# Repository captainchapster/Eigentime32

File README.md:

# Eigentime32

A self-contained digital pocket watch that keeps its own time for a decade. No GPS, one CR2032, one PCB.

*Eigentime* (proper time) is the time a clock measures along its own path, with no outside reference. That is the whole idea here.

## At a glance
| | |
|---|---|
| Timekeeping | Micro Crystal RV-3032-C7 TCXO RTC, ±1.5 ppm (0–50 °C), ~160 nA |
| Display | Sharp LS013B7DH03 1.28" 128×128 memory LCD, powered only while the lid is open |
| MCU | STM32L031G6 (proposed) |
| Wake | Normally-closed reed switch + magnet in the lid |
| Power | CR2032, ~1 µA average, ~10-year target |
| Recalibration | ST25DV04K NFC tag: set time and trim drift from a phone, about once a year |
| Size | 43.9 mm round × 10.8 mm thick with the lid shut (3D-printed hunter case, see `case/`) |

## Accuracy
Aging of the crystal, not temperature, dominates over ten years. With one calibration at build time and a yearly NFC recalibration the target is roughly ±30 s/yr. See [docs/power-pins-accuracy.md](docs/power-pins-accuracy.md).

## Repository layout
- `docs/` design notes and decisions
- `hardware/` KiCad project, BOM
- `firmware/` MCU firmware
- `case/` 3D-printed case: parametric CadQuery model, fit check, printable STL/STEP

## Status
Architecture defined, schematic not started. See [docs/decisions.md](docs/decisions.md).

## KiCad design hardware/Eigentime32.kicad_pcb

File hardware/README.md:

# Hardware

KiCad project goes here (`Eigentime32.kicad_pro`). Schematic order: power → RTC → MCU → LCD → lid/buttons → NFC.

Board: ~40 mm round, 0.8 mm, 2 layers. Front side bare under the LCD; all parts on the back around the CR2032 holder.

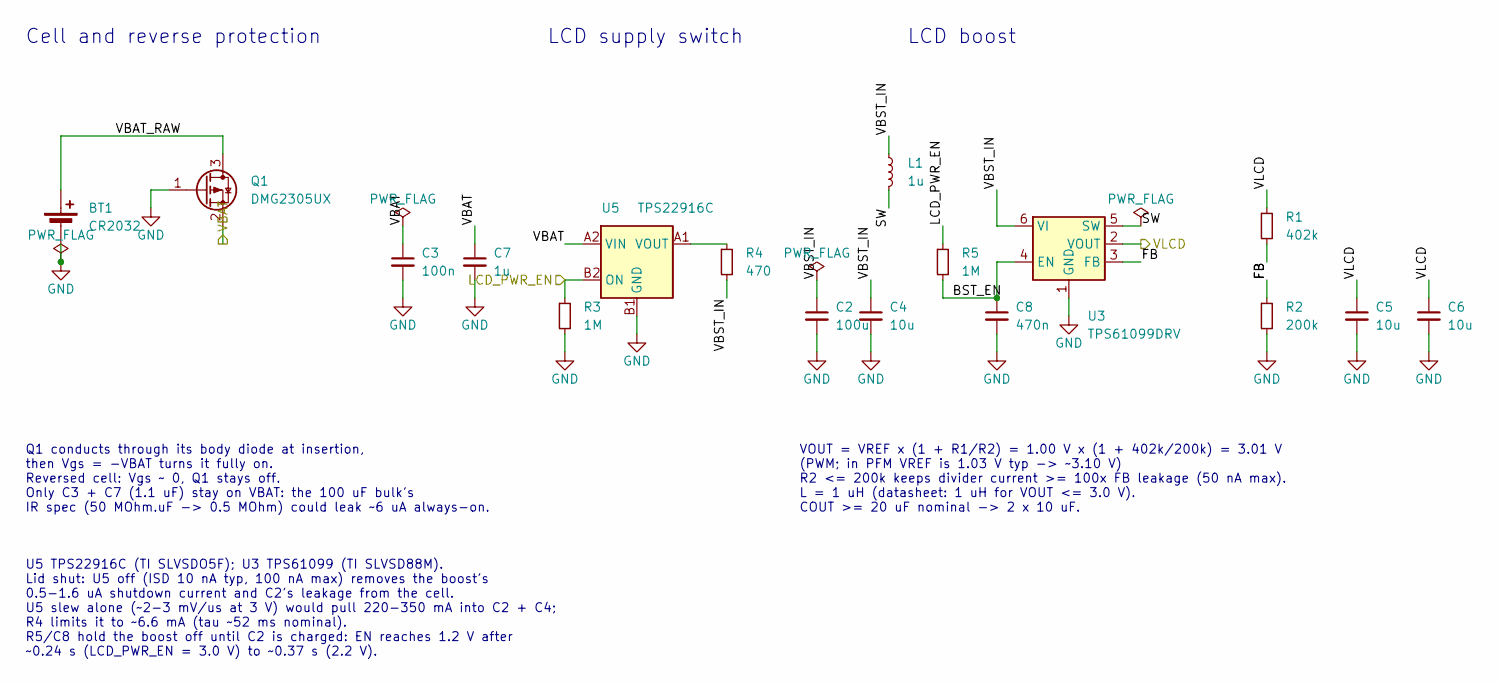
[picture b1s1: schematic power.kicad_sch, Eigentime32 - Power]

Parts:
BT1: CR2032; BatteryHolder_Keystone_3034_1x20mm_SmallNegPad; MPN 3034
C2: 100u; C_1206_3216Metric; MPN CL31A107MQHNNNE
C3: 100n; C_0402_1005Metric; MPN GRM155R71C104KA88D
C4, C5, C6: 10u; C_0603_1608Metric; MPN GRM188R60J106ME84D
C7: 1u; C_0402_1005Metric; MPN GRM155R61A105KE15D
C8: 470n; C_0402_1005Metric; MPN GRM155R61A474KE15D
L1: 1u; L_Wuerth_MAPI-2512; MPN 74404024010
Q1: DMG2305UX; SOT-23; MPN DMG2305UX-7
R1: 402k; R_0402_1005Metric; MPN RC0402FR-07402KL
R2: 200k; R_0402_1005Metric; MPN RC0402FR-07200KL
R3, R5: 1M; R_0402_1005Metric; MPN RC0402FR-071ML
R4: 470; R_0402_1005Metric; MPN RC0402FR-07470RL
U3: TPS61099DRV; WSON-6-1EP_2x2mm_P0.65mm_EP1x1.6mm; MPN TPS61099DRVR
U5: TPS22916C; Texas_PicoStar_BGA-4_0.758x0.758mm_Layout2x2_P0.4mm; MPN TPS22916CYFPR

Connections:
/LCD_PWR_EN: R3.1, R5.1, U5.B2 (ON); also elsewhere on the board
/Power/BST_EN: C8.1, R5.2, U3.4 (EN)
/Power/FB: R1.2, R2.1, U3.3 (FB)
/Power/SW: L1.2, U3.5 (SW)
/Power/VBAT_RAW: BT1.1 (+), Q1.3 (D)
/Power/VBST_IN: C2.1, C4.1, L1.1, R4.2, U3.6 (VI)
/VBAT: C3.1, C7.1, Q1.2 (S), U5.A2 (VIN); also elsewhere on the board
/VLCD: C5.1, C6.1, R1.1, U3.2 (VOUT); also elsewhere on the board
GND: BT1.2 (-), C2.2, C3.2, C4.2, C5.2, C6.2, C7.2, C8.2, Q1.1 (G), R2.2, R3.2, U3.1 (GND), U3.7 (GND), U5.B1 (GND); also elsewhere on the board
unnamed: R4.1, U5.A1 (VOUT)

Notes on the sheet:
Cell and reverse protection
Q1 conducts through its body diode at insertion, then Vgs = -VBAT turns it fully on. Reversed cell: Vgs ~ 0, Q1 stays off. Only C3 + C7 (1.1 uF) stay on VBAT: the 100 uF bulk's IR spec (50 MOhm.uF -> 0.5 MOhm) could leak ~6 uA always-on.
LCD supply switch
LCD boost
U5 TPS22916C (TI SLVSDO5F); U3 TPS61099 (TI SLVSD88M). Lid shut: U5 off (ISD 10 nA typ, 100 nA max) removes the boost's 0.5-1.6 uA shutdown current and C2's leakage from the cell. U5 slew alone (~2-3 mV/us at 3 V) would pull 220-350 mA into C2 + C4; R4 limits it to ~6.6 mA (tau ~52 ms nominal). R5/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
VOUT = VREF x (1 + R1/R2) = 1.00 V x (1 + 402k/200k) = 3.01 V (PWM; in PFM VREF is 1.03 V typ -> ~3.10 V) R2 <= 200k keeps divider current >= 100x FB leakage (50 nA max). L = 1 uH (datasheet: 1 uH for VOUT <= 3.0 V). COUT >= 20 uF nominal -> 2 x 10 uF.

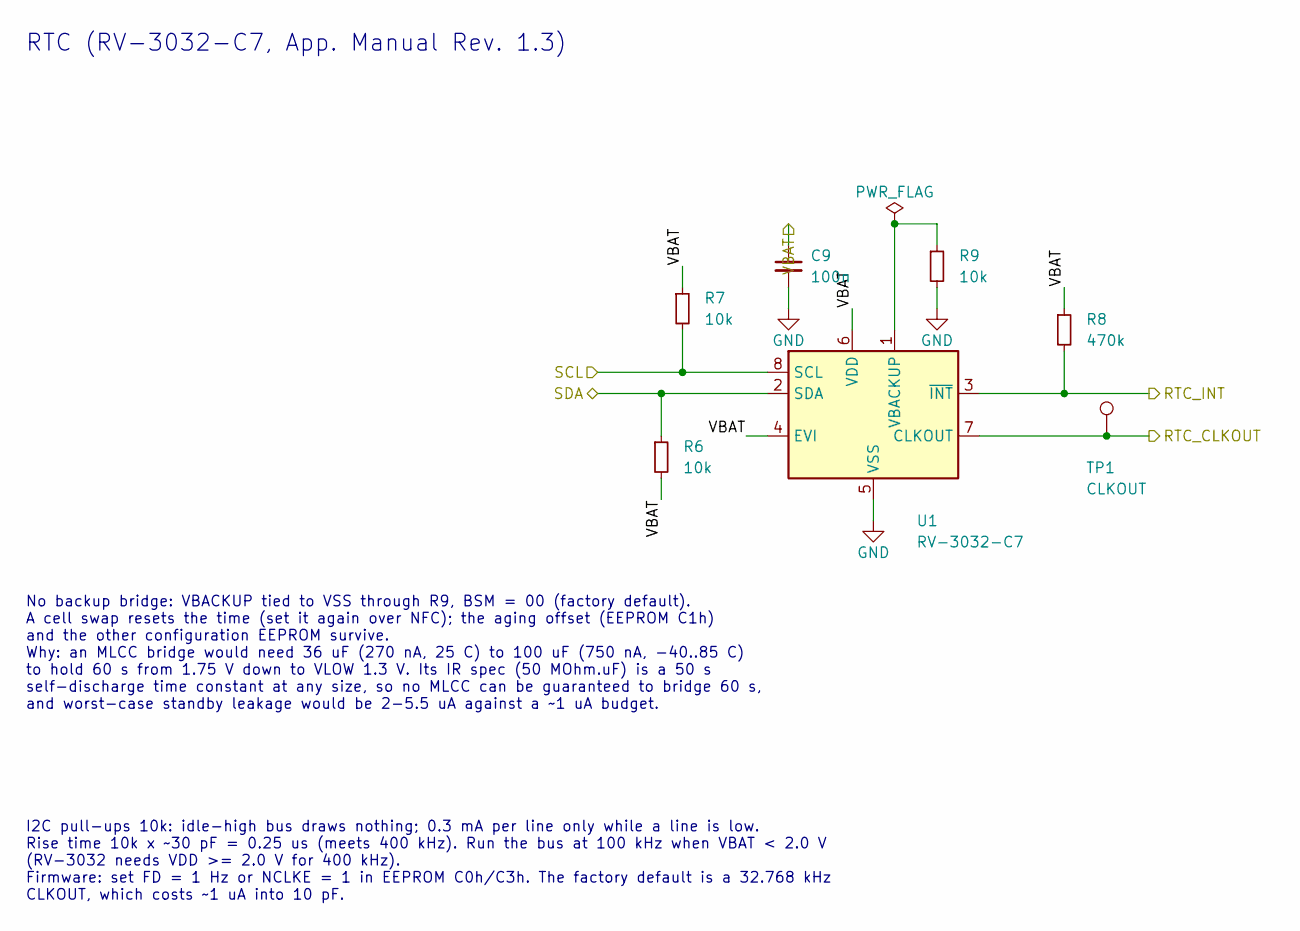
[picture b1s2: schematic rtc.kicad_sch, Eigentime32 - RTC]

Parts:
C9: 100n; C_0402_1005Metric; MPN GRM155R71C104KA88D
R6, R7, R9: 10k; R_0402_1005Metric; MPN RC0402FR-0710KL
R8: 470k; R_0402_1005Metric; MPN RC0402FR-07470KL
TP1: CLKOUT; TestPoint_Pad_D1.0mm
U1: RV-3032-C7; MicroCrystal_C7_SON-8_1.5x3.2mm_P0.9mm; MPN RV-3032-C7 32.768kHz 2.5ppm-TA-QC

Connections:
/RTC_CLKOUT: TP1.1, U1.7 (CLKOUT); also elsewhere on the board
/RTC_INT: R8.2, U1.3 (~INT); also elsewhere on the board
/SCL: R7.2, U1.8 (SCL); also elsewhere on the board
/SDA: R6.1, U1.2 (SDA); also elsewhere on the board
/VBAT: C9.1, R6.2, R7.1, R8.1, U1.4 (EVI), U1.6 (VDD); also elsewhere on the board
GND: C9.2, R9.2, U1.5 (VSS); also elsewhere on the board
unnamed: R9.1, U1.1 (VBACKUP)

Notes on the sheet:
RTC (RV-3032-C7, App. Manual Rev. 1.3)
No backup bridge: VBACKUP tied to VSS through R9, BSM = 00 (factory default). A cell swap resets the time (set it again over NFC); the aging offset (EEPROM C1h) and the other configuration EEPROM survive. Why: an MLCC bridge would need 36 uF (270 nA, 25 C) to 100 uF (750 nA, -40..85 C) to hold 60 s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
I2C pull-ups 10k: idle-high bus draws nothing; 0.3 mA per line only while a line is low. Rise time 10k x ~30 pF = 0.25 us (meets 400 kHz). Run the bus at 100 kHz when VBAT < 2.0 V (RV-3032 needs VDD >= 2.0 V for 400 kHz). Firmware: set FD = 1 Hz or NCLKE = 1 in EEPROM C0h/C3h. The factory default i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

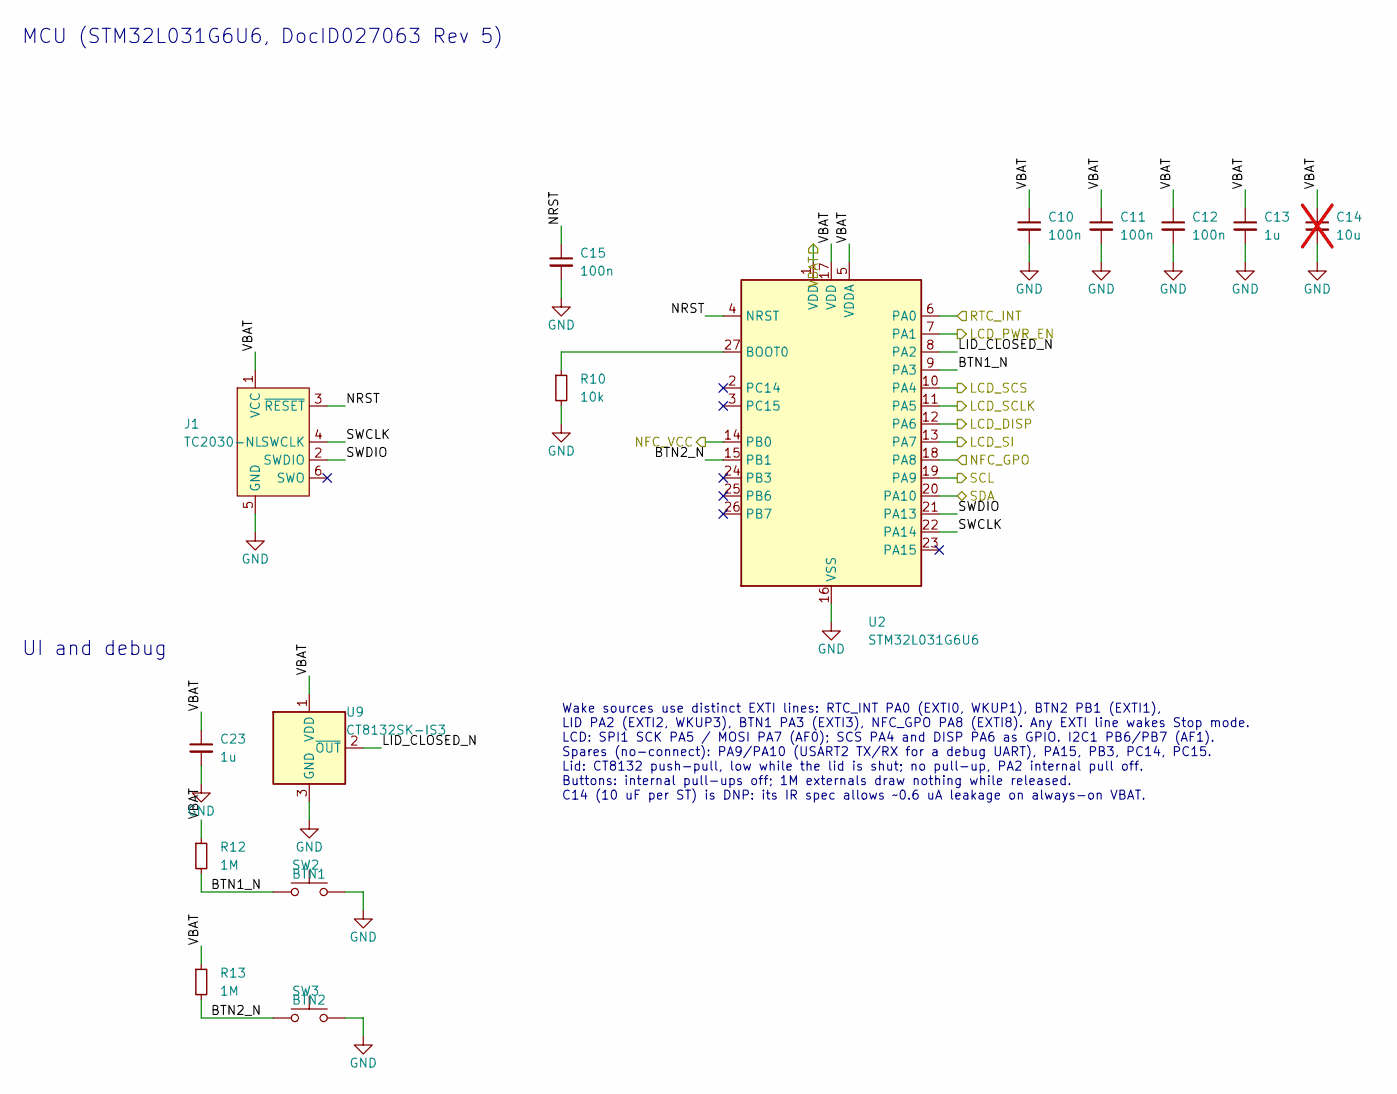
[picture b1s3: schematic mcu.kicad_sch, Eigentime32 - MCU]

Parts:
C10, C11, C12, C15: 100n; C_0402_1005Metric; MPN GRM155R71C104KA88D
C13, C23: 1u; C_0402_1005Metric; MPN GRM155R61A105KE15D
C14: 10u; C_0603_1608Metric; MPN GRM188R60J106ME84D; not fitted
J1: TC2030-NL; Tag-Connect_TC2030-IDC-NL_2x03_P1.27mm_Vertical_FootprintsA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; MPN TC2030-IDC-NL (cable)
R10: 10k; R_0402_1005Metric; MPN RC0402FR-0710KL
R12, R13: 1M; R_0402_1005Metric; MPN RC0402FR-071ML
SW2: BTN1; SW_SPST_EVQP7A; MPN EVQ-P7A01P
SW3: BTN2; SW_SPST_EVQP7A; MPN EVQ-P7A01P
U2: STM32L031G6U6; QFN-28_4x4mm_P0.5mm; MPN STM32L031G6U6
U9: CT8132SK-IS3; SOT-23; MPN CT8132SK-IS3

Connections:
/LCD_DISP: U2.12 (PA6); also elsewhere on the board
/LCD_PWR_EN: U2.7 (PA1); also elsewhere on the board
/LCD_SCLK: U2.11 (PA5); also elsewhere on the board
/LCD_SCS: U2.10 (PA4); also elsewhere on the board
/LCD_SI: U2.13 (PA7); also elsewhere on the board
/MCU/BTN1_N: R12.2, SW2.1, U2.9 (PA3)
/MCU/BTN2_N: R13.2, SW3.1, U2.15 (PB1)
/MCU/LID_CLOSED_N: U2.8 (PA2), U9.2 (~OUT)
/MCU/NRST: C15.1, J1.3 (~RESET), U2.4 (NRST)
/MCU/SWCLK: J1.4 (SWCLK), U2.22 (PA14)
/MCU/SWDIO: J1.2 (SWDIO), U2.21 (PA13)
/NFC_GPO: U2.18 (PA8); also elsewhere on the board
/NFC_VCC: U2.14 (PB0); also elsewhere on the board
/RTC_INT: U2.6 (PA0); also elsewhere on the board
/SCL: U2.19 (PA9); also elsewhere on the board
/SDA: U2.20 (PA10); also elsewhere on the board
/VBAT: C10.1, C11.1, C12.1, C13.1, C14.1, C23.1, J1.1 (VCC), R12.1, R13.1, U2.1 (VDD), U2.5 (VDDA), U2.17 (VDD), U9.1 (VDD); also elsewhere on the board
GND: C10.2, C11.2, C12.2, C13.2, C14.2, C15.2, C23.2, J1.5 (GND), R10.2, SW2.2, SW3.2, U2.16 (VSS), U2.28 (VSS), U9.3 (GND); also elsewhere on the board
unnamed: R10.1, U2.27 (BOOT0)

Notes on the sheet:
MCU (STM32L031G6U6, DocID027063 Rev 5)
UI and debug
Wake sources use distinct EXTI lines: RTC_INT PA0 (EXTI0, WKUP1), BTN2 PB1 (EXTI1), LID PA2 (EXTI2, WKUP3), BTN1 PA3 (EXTI3), NFC_GPO PA8 (EXTI8). Any EXTI line wakes Stop mode. LCD: SPI1 SCK PA5 / MOSI PA7 (AF0); SCS PA4 and DISP PA6 as GPIO. I2C1 PB6/PB7 (AF1). Spares (no-connect): PA9/PA10 (USAR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

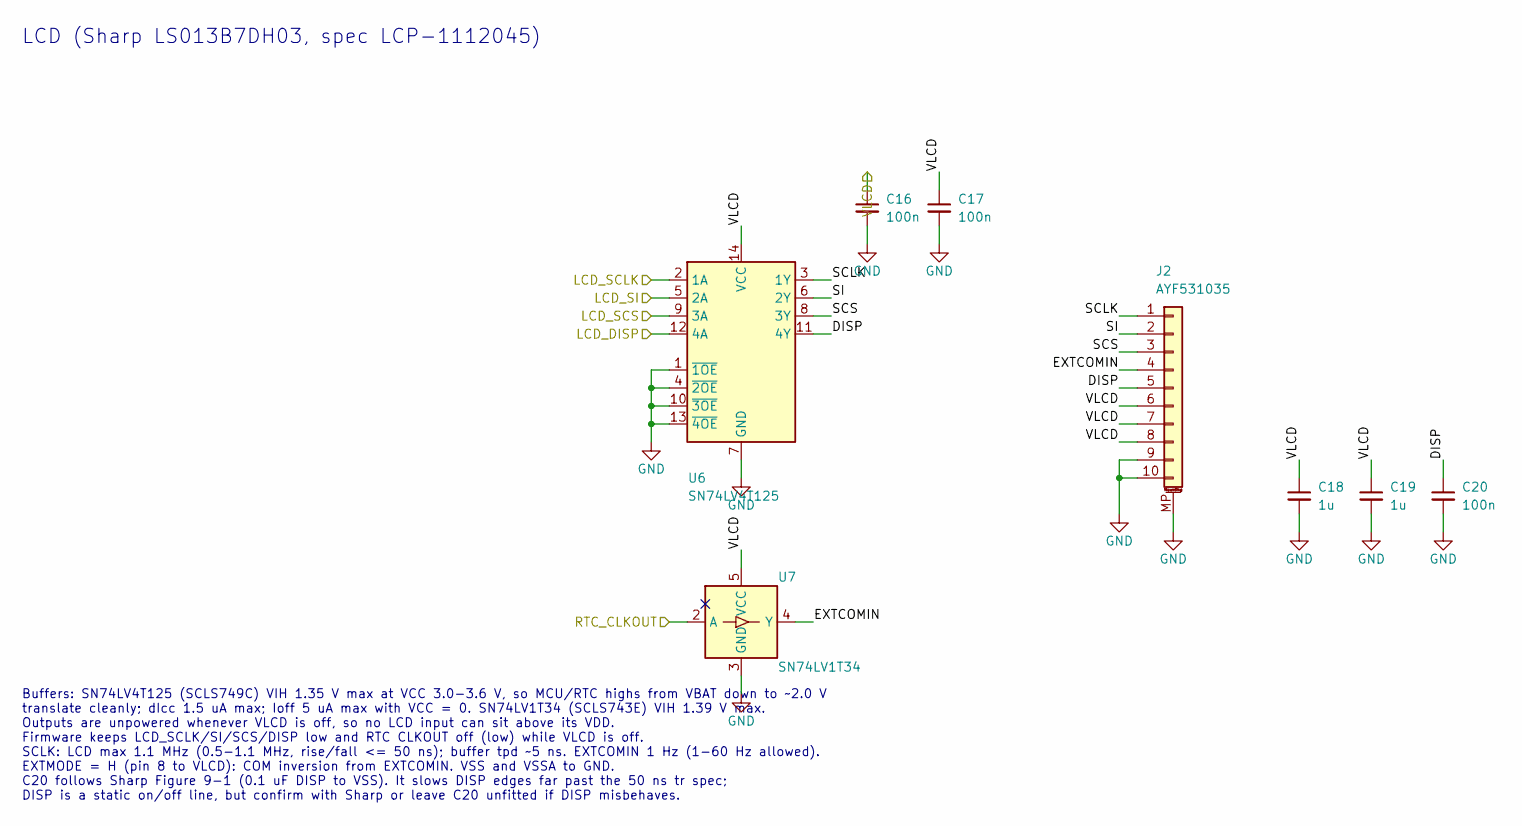
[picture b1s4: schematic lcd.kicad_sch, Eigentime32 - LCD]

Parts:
C16, C17, C20: 100n; C_0402_1005Metric; MPN GRM155R71C104KA88D
C18, C19: 1u; C_0402_1005Metric; MPN GRM155R61A105KE15D
J2: AYF531035; Panasonic_AYF531035_1x10-1MP_P0.5mm_Horizontal; MPN AYF531035
U6: SN74LV4T125; Texas_RGY0014A_VQFN-14-1EP_3.5x3.5mm_P0.5mm_EP2.05x2.05mm; MPN SN74LV4T125RGYR
U7: SN74LV1T34; SOT-353_SC-70-5; MPN SN74LV1T34DCKR

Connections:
/LCD/DISP: C20.1, J2.5, U6.11 (4Y)
/LCD/EXTCOMIN: J2.4, U7.4 (Y)
/LCD/SCLK: J2.1, U6.3 (1Y)
/LCD/SCS: J2.3, U6.8 (3Y)
/LCD/SI: J2.2, U6.6 (2Y)
/LCD_DISP: U6.12 (4A); also elsewhere on the board
/LCD_SCLK: U6.2 (1A); also elsewhere on the board
/LCD_SCS: U6.9 (3A); also elsewhere on the board
/LCD_SI: U6.5 (2A); also elsewhere on the board
/RTC_CLKOUT: U7.2 (A); also elsewhere on the board
/VLCD: C16.1, C17.1, C18.1, C19.1, J2.6, J2.7, J2.8, U6.14 (VCC), U7.5 (VCC); also elsewhere on the board
GND: C16.2, C17.2, C18.2, C19.2, C20.2, J2.9, J2.10, J2.MP (MountPin), U6.1 (~1OE), U6.4 (~2OE), U6.7 (GND), U6.10 (~3OE), U6.13 (~4OE), U6.15 (GND), U7.3 (GND); also elsewhere on the board

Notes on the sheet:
LCD (Sharp LS013B7DH03, spec LCP-1112045)
Buffers: SN74LV4T125 (SCLS749C) VIH 1.35 V max at VCC 3.0-3.6 V, so MCU/RTC highs from VBAT down to ~2.0 V translate cleanly; dIcc 1.5 uA max; Ioff 5 uA max with VCC = 0. SN74LV1T34 (SCLS743E) VIH 1.39 V max. Outputs are unpowered whenever VLCD is off, so no LCD input can sit above its VDD. Firmwar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

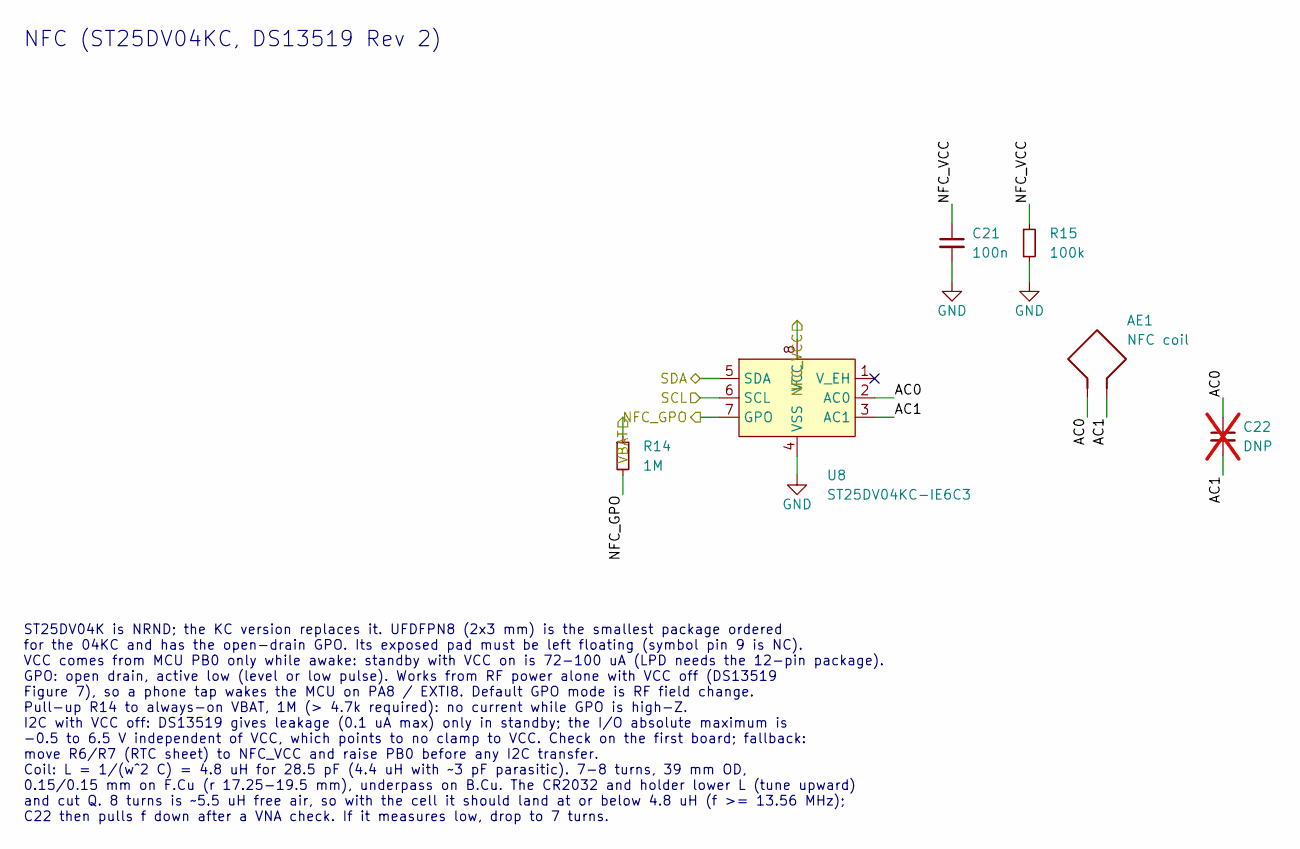
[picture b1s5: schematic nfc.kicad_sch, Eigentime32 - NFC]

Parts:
AE1: NFC coil; NFC_PCB_Coil_D38.1mm_8T
C21: 100n; C_0402_1005Metric; MPN GRM155R71C104KA88D
C22: DNP; C_0402_1005Metric; MPN C0G 0402, value set at tuning; not fitted
R14: 1M; R_0402_1005Metric; MPN RC0402FR-071ML
R15: 100k; R_0402_1005Metric; MPN RC0402FR-07100KL
U8: ST25DV04KC-IE6C3; DFN-8-1EP_3x2mm_P0.5mm_EP1.36x1.46mm; MPN ST25DV04KC-IE6C3

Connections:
/NFC/AC0: AE1.1, C22.1, U8.2 (AC0)
/NFC/AC1: AE1.2, C22.2, U8.3 (AC1)
/NFC_GPO: R14.2, U8.7 (GPO); also elsewhere on the board
/NFC_VCC: C21.1, R15.1, U8.8 (VCC); also elsewhere on the board
/SCL: U8.6 (SCL); also elsewhere on the board
/SDA: U8.5 (SDA); also elsewhere on the board
/VBAT: R14.1; also elsewhere on the board
GND: C21.2, R15.2, U8.4 (VSS); also elsewhere on the board

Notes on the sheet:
NFC (ST25DV04KC, DS13519 Rev 2)
ST25DV04K is NRND; the KC version replaces it. UFDFPN8 (2x3 mm) is the smallest package ordered for the 04KC and has the open-drain GPO. Its exposed pad must be left floating (symbol pin 9 is NC). VCC comes from MCU PB0 only while awake: standby with VCC on is 72-100 uA (LPD needs the 12-pin packag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

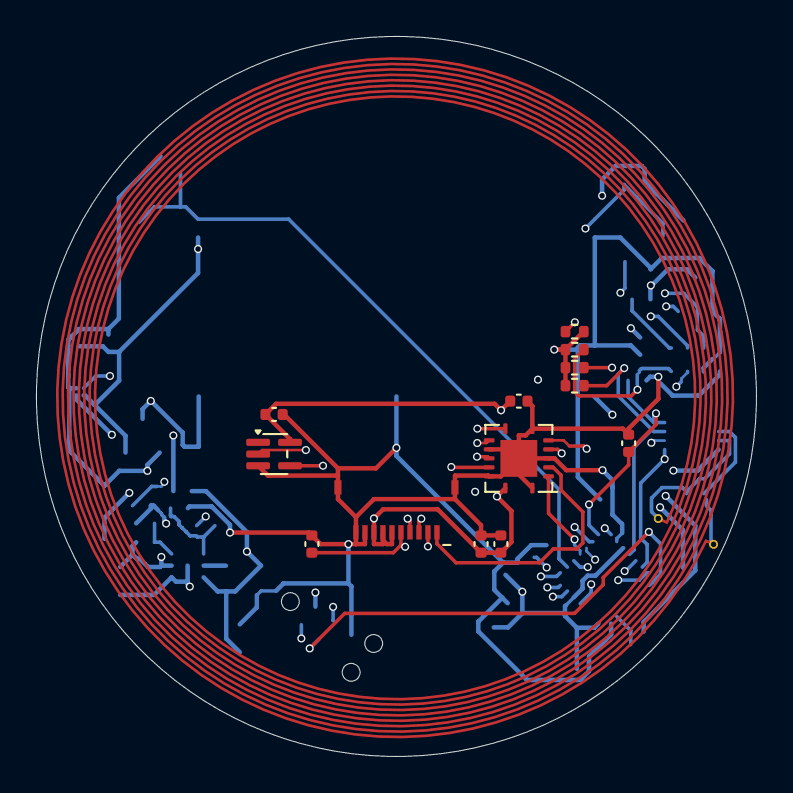
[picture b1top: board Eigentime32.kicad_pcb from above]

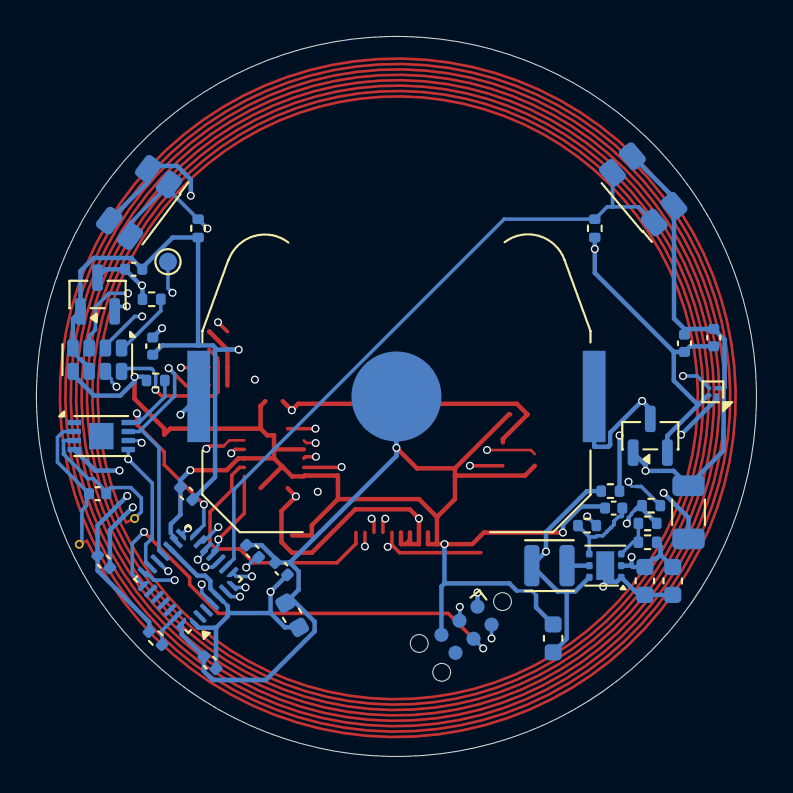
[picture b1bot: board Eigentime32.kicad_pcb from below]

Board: 4 copper layers, 40.0 x 40.0 mm, 53 parts (39 on the bottom side), 35 nets.

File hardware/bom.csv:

Ref,Function,Part,Package,Notes
U1,RTC,Micro Crystal RV-3032-C7 32.768kHz 2.5ppm-TA-QC,C7 SON-8 3.2x1.5 mm,TCXO; CLKOUT 1 Hz to LCD EXTCOMIN; backup switchover off (VBACKUP via R9 to VSS)
U2,MCU,ST STM32L031G6U6,UFQFPN28 4x4 mm,standard pinout (not GxUxS); pin map in docs/power-pins-accuracy.md
U3,LCD boost,TI TPS61099DRVR (adjustable),WSON-6 2x2 mm,VOUT 3.0 V via R1/R2; EN = BST_EN (R5/C8 delay from LCD_PWR_EN)
U5,LCD supply switch,TI TPS22916CYFPR,DSBGA-4 (YFP) 0.78x0.78 mm 0.4 mm pitch,ON = LCD_PWR_EN; isolates boost + C2 from the cell when the lid is shut
U6,LCD SCLK/SI/SCS/DISP buffer,TI SN74LV4T125RGYR,VQFN-14 (RGY) 3.5x3.5 mm,VCC = VLCD; VIH 1.35 V max; Ioff; OE tied low; EP to GND
U7,LCD EXTCOMIN buffer,TI SN74LV1T34DCKR,SC70-5,VCC = VLCD; input from RTC CLKOUT
U8,NFC tag,ST ST25DV04KC-IE6C3,UFDFPN8 2x3 mm,VCC from MCU PB0; open-drain GPO; exposed pad floating (ST25DV04K is NRND)
DS1,Display,Sharp LS013B7DH03,26.6x30.3x0.746 mm module,plugs into J2; not a PCB part
U9,Lid sensor,Allegro CT8132SK-IS3 TMR switch,SOT-23,push-pull active low (lid shut); 10 Hz; 190 nA typ / 900 nA max; replaces the NC reed
SW2-SW3,Time set,Panasonic EVQ-P7A01P side-push tact switch,3.5x2.9x1.35 mm,R12/R13 1M pull-ups; BTN1_N PA3, BTN2_N PB1; actuator at the board edge
BT1,Cell,CR2032 in Keystone 3034 SMT retainer,4.06 mm above board,
C2,Boost input bulk (switched),Samsung CL31A107MQHNNNE 100 uF 6.3 V X5R,1206,
C3,VBAT decoupling (always on),Murata GRM155R71C104KA88D 100 nF 16 V X7R,0402,
C4,Boost CIN,Murata GRM188R60J106ME84D 10 uF 6.3 V X5R,0603,
C5-C6,Boost COUT,Murata GRM188R60J106ME84D 10 uF 6.3 V X5R,0603,20 uF nominal minimum per datasheet
C7,VBAT decoupling / U5 CIN (always on),Murata GRM155R61A105KE15D 1 uF 10 V X5R,0402,
C8,Boost EN delay,Murata GRM155R61A474KE15D 470 nF 10 V X5R,0402,with R5: tau 0.47 s
C9,RTC VDD decoupling,Murata GRM155R71C104KA88D 100 nF 16 V X7R,0402,
C10-C12,MCU VDD/VDDA decoupling,Murata GRM155R71C104KA88D 100 nF 16 V X7R,0402,
C13,MCU VDDA,Murata GRM155R61A105KE15D 1 uF 10 V X5R,0402,
C14,MCU VDD bulk (DNP),Murata GRM188R60J106ME84D 10 uF 6.3 V X5R,0603,not fitted: IR leakage on always-on VBAT
C15,NRST filter,Murata GRM155R71C104KA88D 100 nF 16 V X7R,0402,
C16-C17,Buffer VCC decoupling,Murata GRM155R71C104KA88D 100 nF 16 V X7R,0402,
C18-C19,LCD VDD/VDDA,Murata GRM155R61A105KE15D 1 uF 10 V X5R,0402,Sharp: >= 1 uF each
C20,LCD DISP filter,Murata GRM155R71C104KA88D 100 nF 16 V X7R,0402,Sharp Figure 9-1: DISP to VSS
C21,NFC VCC decoupling,Murata GRM155R71C104KA88D 100 nF 16 V X7R,0402,
C22,NFC tuning (DNP),C0G 0402 value set at tuning,0402,fit only if the coil tunes high
C23,Lid sensor bypass,Murata GRM155R61A105KE15D 1 uF 10 V X5R,0402,datasheet CBYP = 1 uF
L1,Boost inductor,Wurth 74438323010 1.0 uH WE-MAPI,2512 (2.5x2.0x1.2 mm),Isat 2.5 A; 75 mOhm; matches the MAPI-2512 footprint (the WE-LQS 74404024010 named before had a different land pattern and is out of stock)
R1,Boost FB top,Yageo RC0402FR-07402KL 402k 1%,0402,
R2,Boost FB bottom,Yageo RC0402FR-07200KL 200k 1%,0402,
R3,LCD_PWR_EN pull-down,Yageo RC0402FR-071ML 1M 1%,0402,
R4,Inrush limit,Yageo RC0402FR-07470RL 470R 1%,0402,between U5 VOUT and VBST_IN
R5,Boost EN delay,Yageo RC0402FR-071ML 1M 1%,0402,LCD_PWR_EN to BST_EN
R6-R7,I2C pull-ups (SDA/SCL),Yageo RC0402FR-0710KL 10k 1%,0402,to VBAT; draw only while a line is low
R8,RTC INT pull-up,Yageo RC0402FR-07470KL 470k 1%,0402,to VBAT
R9,RTC VBACKUP tie-down,Yageo RC0402FR-0710KL 10k 1%,0402,required when switchover is unused
R10,BOOT0 pull-down,Yageo RC0402FR-0710KL 10k 1%,0402,
R12-R13,Button pull-ups,Yageo RC0402FR-071ML 1M 1%,0402,to VBAT
R14,NFC GPO pull-up,Yageo RC0402FR-071ML 1M 1%,0402,to VBAT; works with VCC off (RF-powered GPO)
R15,NFC_VCC pull-down,Yageo RC0402FR-07100KL 100k 1%,0402,keeps VCC from floating (KC errata)
Q1,Reverse protection,Diodes DMG2305UX-7 P-FET,SOT-23,gate to GND; Vgs(th) -0.9 V max
J1,Programming,Tag-Connect TC2030-IDC-NL pads,TC2030 no-legs,SWDIO/SWCLK/NRST/VBAT/GND
J2,LCD FPC connector,Panasonic AYF531035,0.5 mm 10-pin back lock 1.0 mm high,top and bottom contact; project footprint from Panasonic land pattern
AE1,NFC antenna,PCB loop coil (F.Cu),38.1 mm OD 8 turns 0.15/0.15 mm,~5.1 uH free air; target ~4.8 uH with 28.5 pF internal; not a BOM part
TP1,RTC CLKOUT test pad,Test pad,1.0 mm pad,1 Hz accuracy measurement

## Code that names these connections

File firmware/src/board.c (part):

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    RCC->APB1ENR |= RCC_APB1ENR_PWREN;

    /* outputs, all off: LCD power, LCD lines, NFC supply */
    pin_set(GPIOA, PIN_LCD_PWR_EN, 0);
    pin_mode(GPIOA, PIN_LCD_PWR_EN, 1);
    lcd_pins_idle();
    pin_set(GPIOB, PIN_NFC_VCC, 0);
    pin_mode(GPIOB, PIN_NFC_VCC, 1);

    /* inputs with external pull-ups (or push-pull drivers): no internal pulls */
    pin_mode(GPIOA, PIN_RTC_INT, 0);
    pin_mode(GPIOA, PIN_LID_CLOSED, 0);
    pin_mode(GPIOA, PIN_BTN1, 0);
    pin_mode(GPIOA, PIN_NFC_GPO, 0);
    pin_mode(GPIOB, PIN_BTN2, 0);

    /* EXTI: PA0 (RTC, falling), PB1 (BTN2, falling), PA2 (lid, both), PA3 (BTN1, falling), PA8 (NFC, falling) */
    SYSCFG->EXTICR[0] = (SYSCFG->EXTICR[0] & ~(0xFu << 4)) | (1u << 4); /* EXTI1 <- port B */
    uint32_t lines = (1u << 0) | (1u << 1) | (1u << 2) | (1u << 3) | (1u << 8);
    EXTI->FTSR |= lines;
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bool btn2_down(void) { return !pin_get(GPIOB, PIN_BTN2); }

/* ---------------------------------------------------------------- LCD */
void lcd_power(bool on) { pin_set(GPIOA, PIN_LCD_PWR_EN, on); }

void lcd_pins_idle(void)
{
    static const int pins[] = {PIN_LCD_SCS, PIN_LCD_SCLK, PIN_LCD_DISP, PIN_LCD_SI};
    for (unsigned i = 0; i < sizeof pins / sizeof pins[0]; i++) {
        pin_set(GPIOA, pins[i], 0);
        pin_mode(GPIOA, pins[i], 1);
    }
}

void lcd_disp(bool on) { pin_set(GPIOA, PIN_LCD_DISP, on); }
void lcd_scs(bool on) { pin_set(GPIOA, PIN_LCD_SCS, on); }

void spi_open(void)
{
    RCC->APB2ENR |= RCC_APB2ENR_SPI1EN;
    pin_af(GPIOA, PIN_LCD_SCLK, 0);
    pin_af(GPIOA, PIN_LCD_SI, 0);
    /* master, mode 0, LSB first, fPCLK/4 = 524 kHz (LCD max 1 MHz), software NSS */
    SPI1->CR1 = SPI_CR1_MSTR | SPI_CR1_LSBFIRST | SPI_CR1_BR_0 | SPI_CR1_SSM | SPI_CR1_SSI;
    SPI1->CR1 |= SPI_CR1_SPE;
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}

/* ---------------------------------------------------------------- NFC supply */
void nfc_power(bool on) { pin_set(GPIOB, PIN_NFC_VCC, on); }

/* ---------------------------------------------------------------- I2C1 */
static void i2c_open(void)
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
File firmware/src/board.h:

/* Eigentime32 pin map (docs/power-pins-accuracy.md section 5) and low-level helpers. */
#ifndef BOARD_H
#define BOARD_H

#include <stdbool.h>
#include <stddef.h>
#include <stdint.h>

#include "stm32l0xx.h"

/* Port A */
#define PIN_RTC_INT     0   /* EXTI0, active low */
#define PIN_LCD_PWR_EN  1   /* load switch ON + boost EN (RC delayed) */
#define PIN_LID_CLOSED  2   /* EXTI2, low while the lid magnet is near */
#define PIN_BTN1        3   /* EXTI3, 10 o'clock, active low */
#define PIN_LCD_SCS     4
#define PIN_LCD_SCLK    5   /* SPI1_SCK AF0 */
#define PIN_LCD_DISP    6
#define PIN_LCD_SI      7   /* SPI1_MOSI AF0 */
#define PIN_NFC_GPO     8   /* EXTI8, open drain, low on an RF write */
#define PIN_SCL         9   /* I2C1 AF1 */
#define PIN_SDA         10  /* I2C1 AF1 */
/* Port B */
#define PIN_NFC_VCC     0
#define PIN_BTN2        1   /* EXTI1, 2 o'clock, active low */

#define CORE_HZ 2097152u    /* MSI range 5, the reset default */

/* wake/event flags set from interrupts */
#define EV_RTC   (1u << 0)
#define EV_LID   (1u << 1)
#define EV_BTN1  (1u << 2)
#define EV_BTN2  (1u << 3)
#define EV_NFC   (1u << 4)

void board_init(void);
uint32_t board_take_events(void);
void board_drop_events(uint32_t mask);
void board_sleep(void);                /* Stop mode until an EXTI wake */
void delay_ms(uint32_t ms);
uint32_t millis(void);                 /* only counts while the core runs */

bool lid_open(void);
bool btn1_down(void);
bool btn2_down(void);

void lcd_power(bool on);               /* load switch; boost follows after ~0.3 s */
void lcd_pins_idle(void);              /* hold SCS/SCLK/SI/DISP low while VLCD is off */
void lcd_disp(bool on);
void lcd_scs(bool on);
void spi_open(void);
void spi_close(void);
void spi_write(const uint8_t *buf, size_t n);

void nfc_power(bool on);

bool i2c_write(uint8_t addr7, const uint8_t *buf, size_t n);
bool i2c_write_read(uint8_t addr7, const uint8_t *wbuf, size_t wn, uint8_t *rbuf, size_t rn);

uint16_t battery_mv(void);             /* VDD from VREFINT */

/* STM32 data EEPROM (1 KB at DATA_EEPROM_BASE) */
void eeprom_write_words(uint32_t offset, const uint32_t *src, size_t words);
void eeprom_read(uint32_t offset, void *dst, size_t n);

#endif
